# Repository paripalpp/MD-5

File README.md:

# MD-5
my 5th motor driver
# firmware
[MD-5_firm](paripalpp/MD-5_firm)
## LISENCE
<br />This work is licensed under a <a rel="license" href="http://creativecommons.org/licenses/by/4.0/">Creative Commons Attribution 4.0 International License</a>.
<br />この 作品 は <a rel="license" href="http://creativecommons.org/licenses/by/4.0/">クリエイティブ・コモンズ 表示 4.0 国際 ライセンス</a>の下に提供されています。

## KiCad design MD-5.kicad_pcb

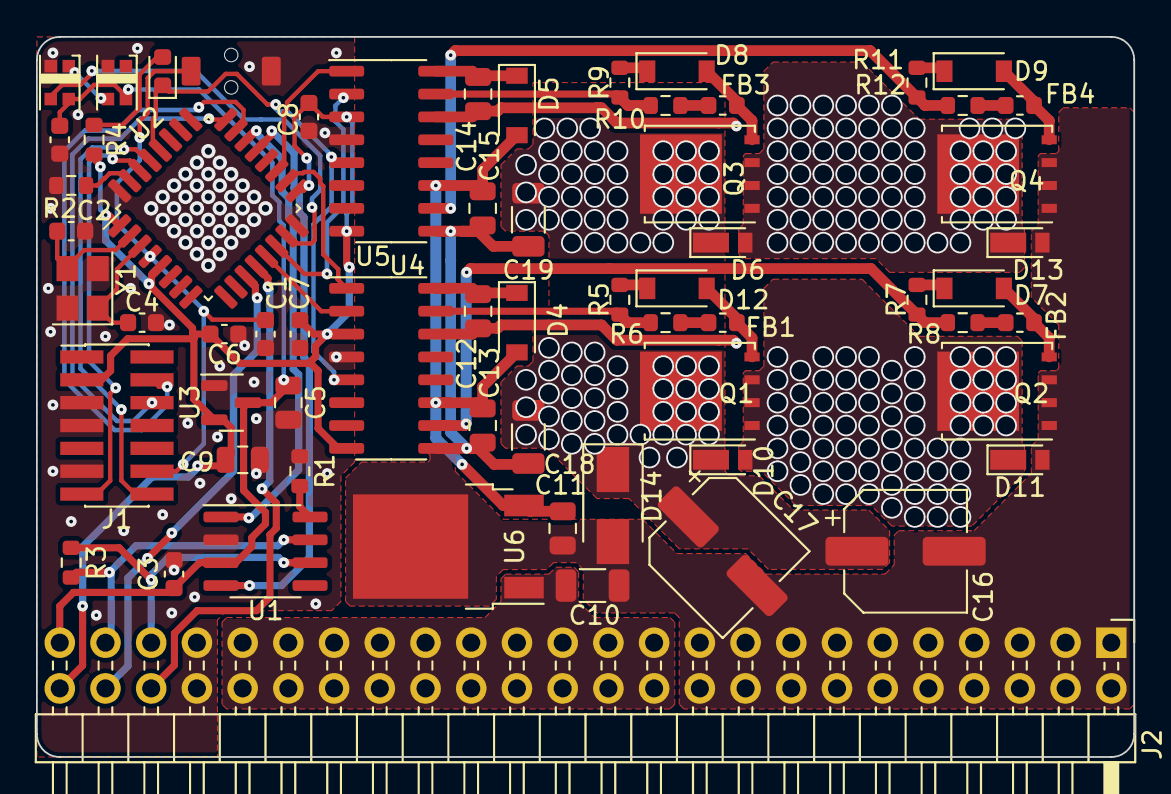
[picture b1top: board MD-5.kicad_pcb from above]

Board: 2 copper layers, 61.0 x 40.0 mm, 65 parts (1 on the bottom side), 49 nets.

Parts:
C1, C3, C6, C7, C8, C20: 0.1uF; C_0603_1608Metric
C2, C4: 22pF; C_0603_1608Metric
C5, C9, C11, C12, C13, C14, C15: 10uF; C_0805_2012Metric
C10, C18, C19: 10uF; C_1206_3216Metric
C16, C17: 33uF; CP_Elec_6.3x7.7
D1, D2: WS2812C; LED_2020Metric_WS2812C_2.0x2.0mm_P1.0mm
D3: LED; LED_0603_1608Metric
D4, D5, D6, D7, D8, D9: 1N4148W; D_SOD-123
D10, D11, D12, D13: CUHS20S60H3F; D_US2A
D14: D_TVS; D_SMA
FB1, FB2, FB3, FB4: 60Ohm 100MHz; L_0603_1608Metric
J1: Conn_02x07_Odd_Even; PinHeader_2x07_P1.27mm_Vertical_SMD
J2: Header_hol_02x24; PinHeader_2x24_P2.54mm_Horizontal
J3: Output; T_connecter_female_horizontal
Q1, Q2, Q3, Q4: BSC025N08LS5; TDSON-8-1
R1, R2, R4: 10kR; R_0603_1608Metric
R3: 120R; R_0603_1608Metric
R5, R7, R9, R11: 5R; R_0603_1608Metric
R6, R8, R10, R12: 7.5R; R_0603_1608Metric
SW1: SW_Push; TVAF06-A020B-R
U1: MCP2551-I-SN; SOIC-8_3.9x4.9mm_P1.27mm
U2: STM32F303K8Tx; LQFP-32_7x7mm_P0.8mm
U3: MCP1792-3302H; SOT-23
U4, U5: 2EDF7175; SOIC-16_3.9x9.9mm_P1.27mm
U6: L7812; TO-252-2
Y1: 16MHz; Crystal_SMD_3225-4Pin_3.2x2.5mm

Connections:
+3V3: C6.1, C7.1, C8.1, C9.1, J1.3, J2.48, R4.2, U2.1 (VDD), U2.5 (VDDA), U2.17 (VDD), U3.2 (VO), U4.3 (VDDI), U4.8 (SLDON), U5.3 (VDDI), U5.8 (SLDON)
+5V: C3.1, C5.1, C20.1, D1.4 (VDD), D2.4 (VDD), J2.47, U1.3 (VDD), U3.3 (VI)
+12V: C11.1, C13.1, C15.1, D4.2 (A), D5.2 (A), U4.11 (VDDB), U5.11 (VDDB), U6.3 (OUT)
/AHG: R5.2, R6.1, U4.15 (OUTA)
/AHIN: U2.18 (PA8), U4.1 (INA)
/ALG: R7.2, R8.2, U4.10 (OUTB)
/ALIN: U2.13 (PA7), U4.2 (INB)
/AOUT: C12.2, D10.2 (A), D11.1 (K), J3.1, Q1.1 (S), Q1.2 (S), Q1.3 (S), Q2.5 (D), U4.14 (GNDA)
/BHG: R9.2, R10.1, U5.15 (OUTA)
/BHIN: U2.19 (PA9), U5.1 (INA)
/BLG: R11.2, R12.2, U5.10 (OUTB)
/BLIN: U2.14 (PB0), U5.2 (INB)
/BOOT0: R2.2, U2.31 (BOOT0)
/BOUT: C14.2, D12.2 (A), D13.1 (K), J3.2, Q3.1 (S), Q3.2 (S), Q3.3 (S), Q4.5 (D), U5.14 (GNDA)
/CANH: J2.45, R3.1, U1.7 (CANH)
/CANL: J2.43, R3.2, U1.6 (CANL)
/CAN_RX: U1.4 (RXD), U2.21 (PA11)
/CAN_TX: U1.1 (TXD), U2.22 (PA12)
/DISABLE: D3.1 (K), U2.28 (PB5), U4.5 (DISABLE), U5.5 (DISABLE)
/NRST: C1.1, J1.12, SW1.2, U2.4 (NRST)
/NeoPixel: D1.3 (DIN), U2.15 (PB1)
/OSC_IN: C2.1, U2.2 (PF0), Y1.3
/OSC_OUT: C4.1, U2.3 (PF1), Y1.1
/PWM_IN1: J2.46, U2.11 (PA5)
/PWM_IN2: J2.44, U2.12 (PA6)
/SWCLK: J1.6, U2.24 (PA14)
/SWDIO: J1.4, U2.23 (PA13)
/VCP_RX: J1.13, U2.30 (PB7)
/VCP_TX: J1.14, U2.29 (PB6)
GND: C1.2, C2.2, C3.2, C4.2, C5.2, C6.2, C7.2, C8.2, C9.2, C20.2, D1.2 (VSS), D2.2 (VSS), J1.5, J1.7, J1.11, J2.41, J2.42, R1.1, R2.1, SW1.1, U1.2 (VSS), U2.16 (VSS), U2.32 (VSS), U3.1 (GND), U4.4 (GNDI), U5.4 (GNDI), Y1.2, Y1.4
GNDPWR: C10.2, C11.2, C13.2, C15.2, C16.2, C17.2, C18.2, C19.2, D11.2 (A), D13.2 (A), D14.2 (A2), J2.1, J2.2, J2.3, J2.4, J2.5, J2.6, J2.7, J2.8, J2.9, J2.10, J2.11, J2.12, J2.13, J2.14, J2.15, J2.16, J2.17, J2.18, J2.19, J2.20, Q2.1 (S), Q2.2 (S), Q2.3 (S), Q4.1 (S), Q4.2 (S), Q4.3 (S), U4.9 (GNDB), U5.9 (GNDB), U6.2 (GND)
unnamed: C12.1, D4.1 (K), U4.16 (VDDA)
unnamed: C14.1, D5.1 (K), U5.16 (VDDA)
unnamed: D1.1 (DOUT), D2.3 (DIN)
unnamed: D3.2 (A), R4.1
unnamed: D6.1 (K), R5.1
unnamed: D6.2 (A), FB1.2, Q1.4 (G)
unnamed: D7.1 (K), R7.1
unnamed: D7.2 (A), FB2.2, Q2.4 (G)
unnamed: D8.1 (K), R9.1
unnamed: D8.2 (A), FB3.2, Q3.4 (G)
unnamed: D9.1 (K), R11.1
unnamed: D9.2 (A), FB4.2, Q4.4 (G)
unnamed: FB1.1, R6.2
unnamed: FB2.1, R8.1
unnamed: FB3.1, R10.2
unnamed: FB4.1, R12.1
unnamed: R1.2, U1.8 (Rs)
VCC: C10.1, C16.1, C17.1, C18.1, C19.1, D10.1 (K), D12.1 (K), D14.1 (A1), J2.21, J2.22, J2.23, J2.24, J2.25, J2.26, J2.27, J2.28, J2.29, J2.30, J2.31, J2.32, J2.33, J2.34, J2.35, J2.36, J2.37, J2.38, J2.39, J2.40, Q1.5 (D), Q3.5 (D), U6.1 (IN)

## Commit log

2021-12-26 initt project in 5.0
2021-12-26 chenged to 6.0
2021-12-26 harf bridge
2022-01-02 maikontuika
2022-01-04 CANHL
2022-01-05 mcushuuhen
2022-01-06 sche fin?
2022-01-09 うわーー
2022-01-10 3d model added
2022-02-19 comp
2022-02-19 garbar
2022-02-19 silk
